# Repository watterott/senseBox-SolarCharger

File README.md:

# senseBox SolarCharger
SolarCharger extension for the senseBox MCU

* senseBox SolarCharger for up to 2x 18650 LiPo batteries
* 7-24V Solar input voltage
* Open-Source and released under the [Creative Commons Attribution Share-Alike License](https://creativecommons.org/licenses/by-sa/4.0/).
* **[Documentation on learn.watterott.com](https://learn.watterott.com)**

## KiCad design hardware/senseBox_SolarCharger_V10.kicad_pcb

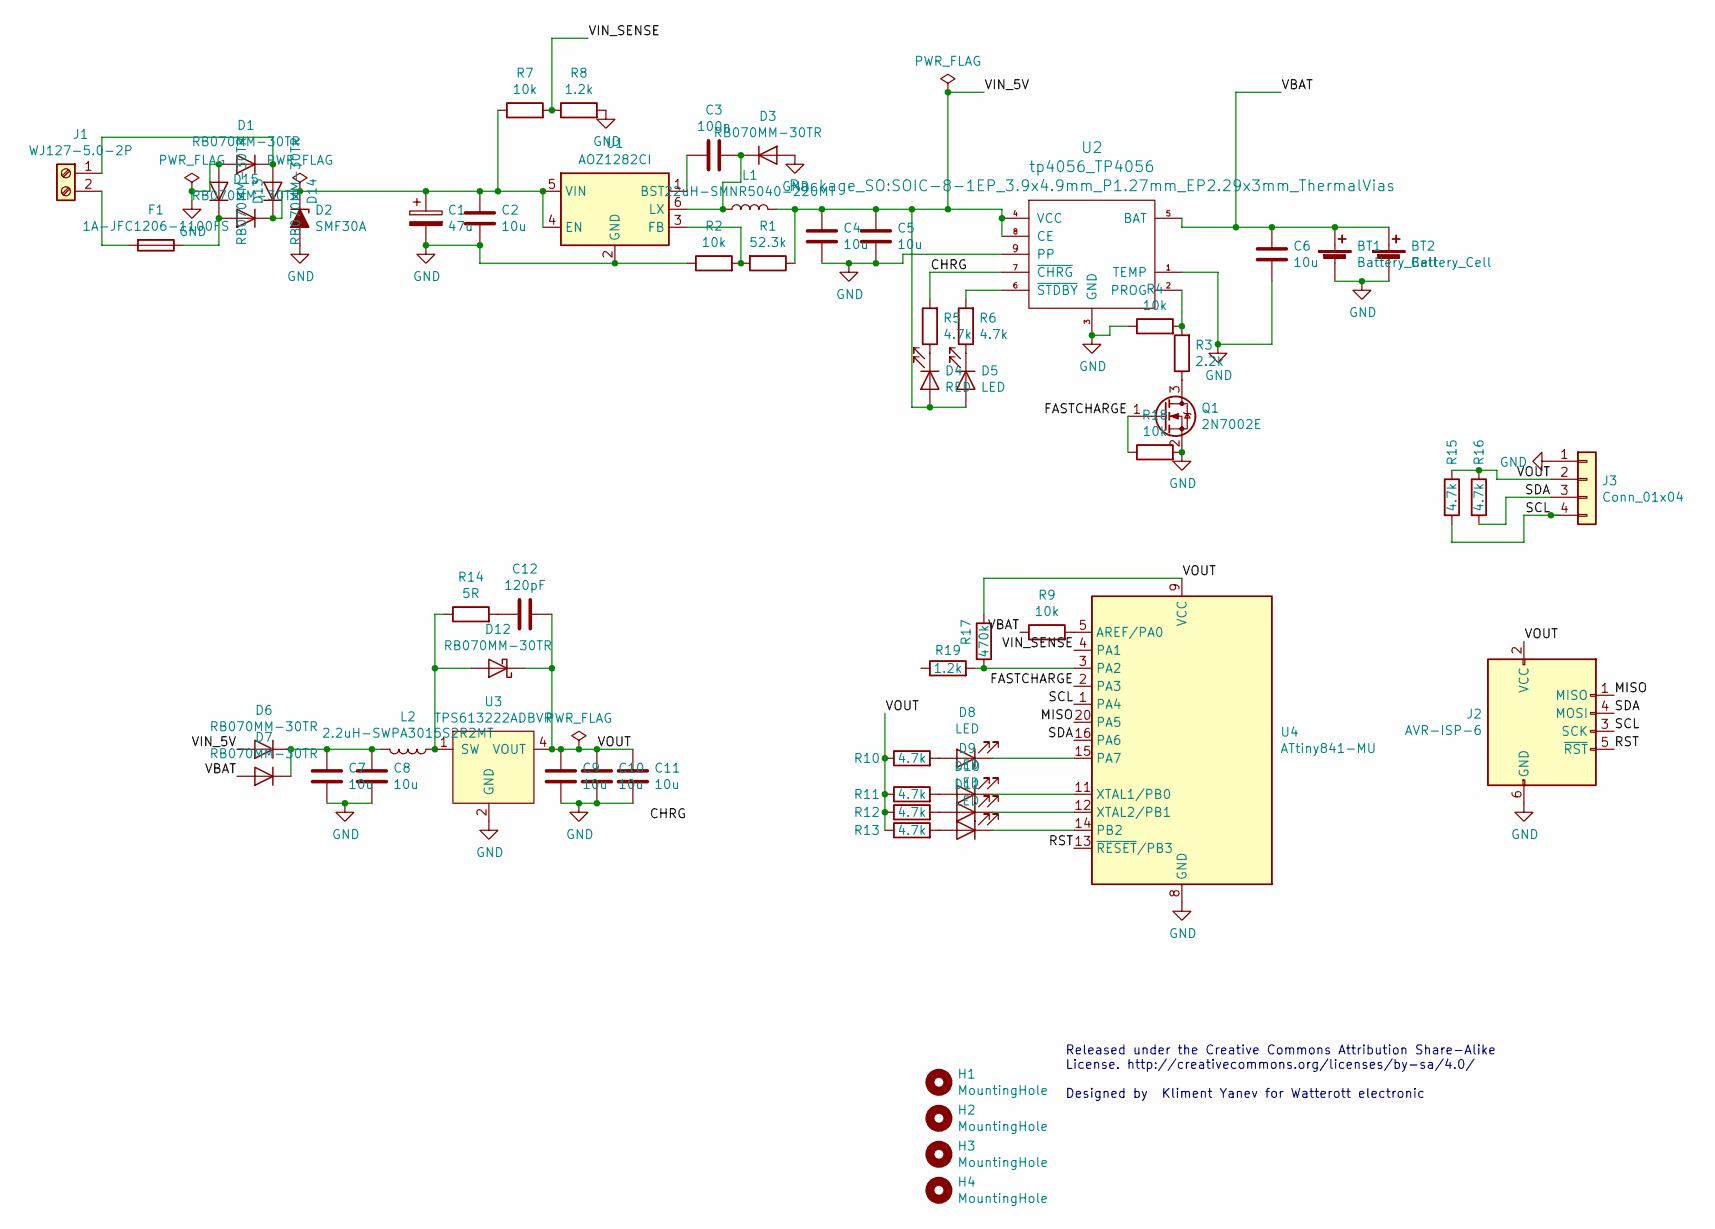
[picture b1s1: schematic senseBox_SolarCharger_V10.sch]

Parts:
BT1, BT2: Battery_Cell; Keystone-54x2-18650
C1: 47u; C_6.3MM
C2, C4, C5, C6, C7, C8, C9, C10, C11: 10u; C1206
C3: 100n; C0603
C12: 120pF; C0603
D1, D6, D7, D13, D14, D15: RB070MM-30TR; D_SOD-123
D2: SMF30A; SOD123
D3, D12: RB070MM-30TR; SOD123
D4: RED; LED_0603_1608Metric
D5, D8, D9, D10, D11: LED; LED_0603_1608Metric
F1: 1A-JFC1206-1100FS; Fuse_1206_3216Metric_Castellated
H1, H2, H3, H4: MountingHole; MountingHole_3.5mm
J1: WJ127-5.0-2P; TerminalBlock_Altech_AK300-2_P5.00mm
J2: AVR-ISP-6; MA03-2
J3: Conn_01x04; JST_B4B-PH-SM4-TB
L1: 22uH-SMNR5040-220MT; L_Wuerth_WE-PD2-Typ-MS
L2: 2.2uH-SWPA3015S2R2MT; L_Neosid_SMS-ME3010
Q1: 2N7002E; SOT-23
R1: 52.3k; R_0603_1608Metric
R2, R4, R7, R9, R18: 10k; R_0603_1608Metric
R3: 2.2k; R_0603_1608Metric
R5, R6, R10, R11, R12, R13, R15, R16: 4.7k; R_0603_1608Metric
R8, R19: 1.2k; R_0603_1608Metric
R14: 5R; R_0603_1608Metric
R17: 470k; R_0603_1608Metric
U1: AOZ1282CI; SOT23-6
U2: tp4056_TP4056; SOIC-8-1EP_3.9x4.9mm_P1.27mm_EP2.29x3mm_ThermalVias
U3: TPS613222ADBVR; SOT23-5
U4: ATtiny841-MU; QFN20-PAD

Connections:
/CHRG: R5.2, R19.1, U2.7 (~CHRG)
/FASTCHARGE: Q1.1 (G), R18.1, U4.2 (PA3)
/MISO: J2.1 (MISO), U4.20 (PA5)
/RST: J2.5 (~RST), U4.13 (~RESET~/PB3)
/SCL: J2.3 (SCK), J3.4, R15.2, U4.1 (PA4)
/SDA: J2.4 (MOSI), J3.3, R16.2, U4.16 (PA6)
/VBAT: BT1.1 (+), BT2.1 (+), C6.1, D7.2 (A), R9.1, U2.5 (BAT)
/VIN_5V: C4.1, C5.1, D4.2 (A), D5.2 (A), D6.2 (A), L1.2, R1.1, U2.4 (VCC), U2.8 (CE)
/VIN_SENSE: R7.2, R8.1, U4.4 (PA1)
/VOUT: C9.1, C10.1, C11.1, C12.1, D12.1 (K), J2.2 (VCC), J3.2, R10.1, R11.1, R12.1, R13.1, R15.1, R16.1, R17.1, U3.4 (VOUT), U4.9 (VCC)
GND: BT1.2 (-), BT2.2 (-), C1.2, C2.2, C4.2, C5.2, C6.2, C7.2, C8.2, C9.2, C10.2, C11.2, D1.2 (A), D2.2 (A), D3.2 (A), D13.2 (A), J2.6 (GND), J3.1, Q1.2 (S), R2.1, R4.1, R8.2, R18.2, U1.2 (GND), U2.1 (TEMP), U2.3 (GND), U2.9 (PP), U3.2 (GND), U4.8 (GND), U4.21 (GND)
unnamed: C1.1, C2.1, D2.1 (K), D14.1 (K), D15.1 (K), R7.1, U1.4 (EN), U1.5 (VIN)
unnamed: C3.1, D3.1 (K), L1.1, U1.6 (LX)
unnamed: C3.2, U1.1 (BST)
unnamed: C7.1, C8.1, D6.1 (K), D7.1 (K), L2.2
unnamed: C12.2, R14.2
unnamed: D1.1 (K), D14.2 (A), J1.1
unnamed: D4.1 (K), R5.1
unnamed: D5.1 (K), R6.1
unnamed: D8.1 (K), U4.15 (PA7)
unnamed: D8.2 (A), R10.2
unnamed: D9.1 (K), U4.11 (XTAL1/PB0)
unnamed: D9.2 (A), R11.2
unnamed: D10.1 (K), U4.12 (XTAL2/PB1)
unnamed: D10.2 (A), R12.2
unnamed: D11.1 (K), U4.14 (PB2)
unnamed: D11.2 (A), R13.2
unnamed: D12.2 (A), L2.1, R14.1, U3.1 (SW)
unnamed: D13.1 (K), D15.2 (A), F1.1
unnamed: F1.2, J1.2
unnamed: Q1.3 (D), R3.1
unnamed: R1.2, R2.2, U1.3 (FB)
unnamed: R3.2, R4.2, U2.2 (PROG)
unnamed: R6.2, U2.6 (~STDBY)
unnamed: R9.2, U4.5 (AREF/PA0)
unnamed: R17.2, R19.2, U4.3 (PA2)

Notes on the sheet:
Released under the Creative Commons Attribution Share-Alike License. http://creativecommons.org/licenses/by-sa/4.0/ Designed by Kliment Yanev for Watterott electronic

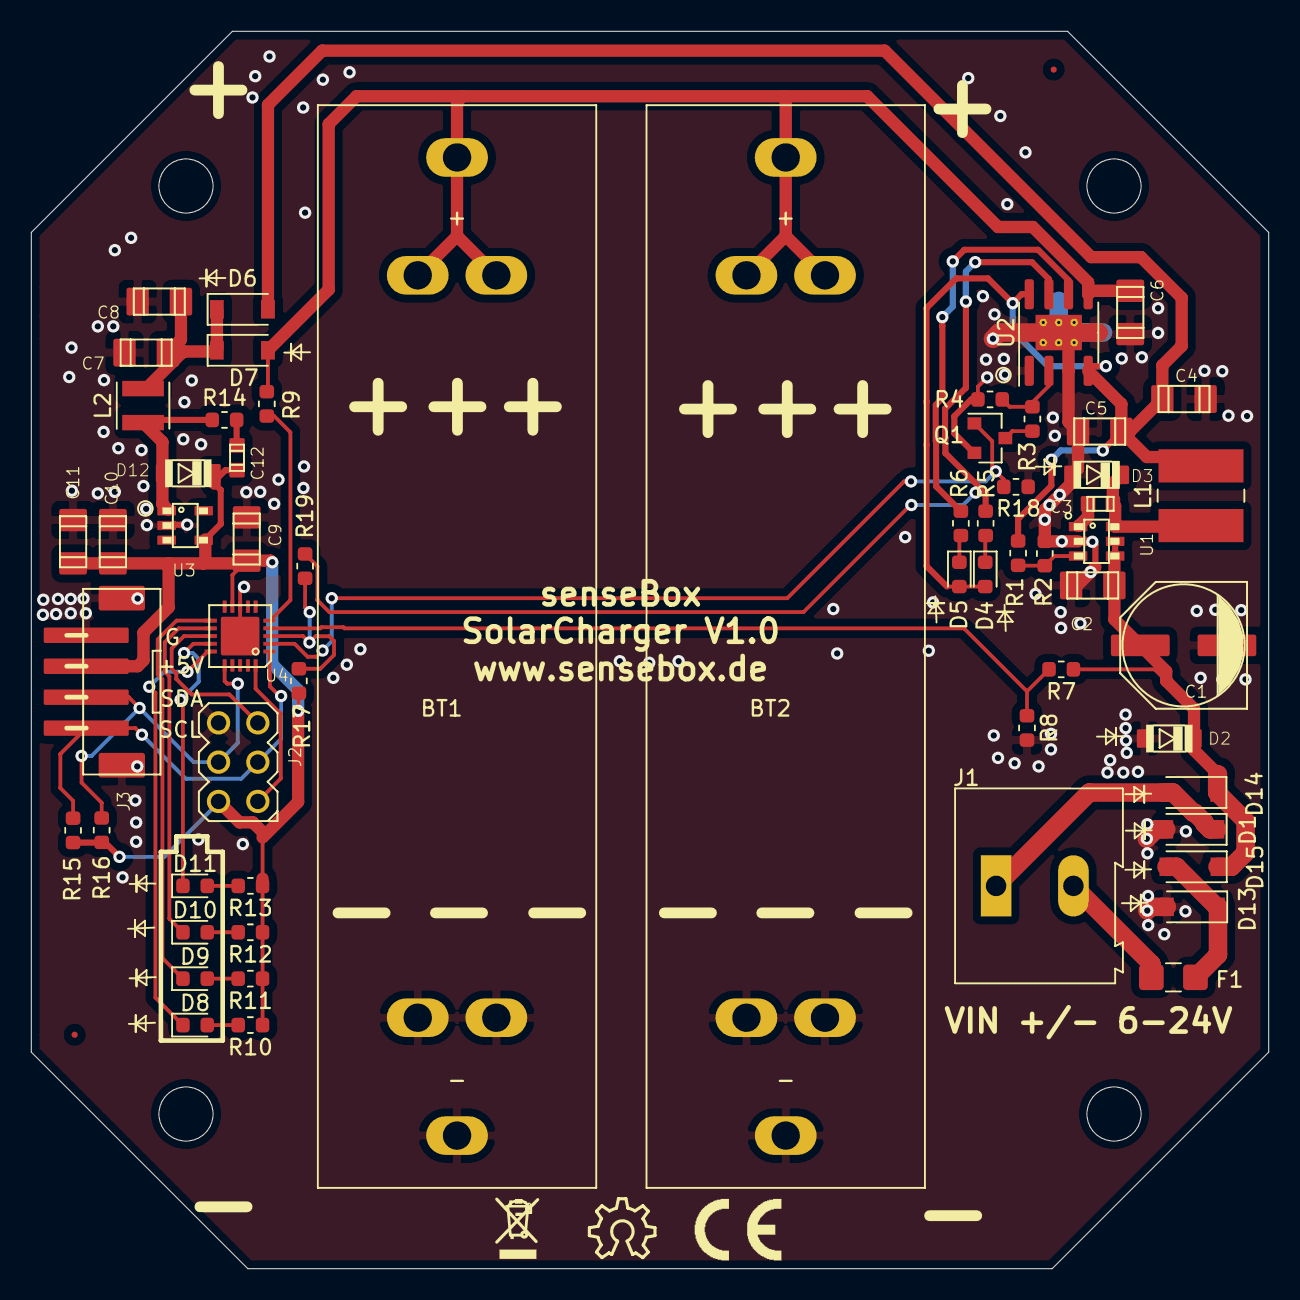
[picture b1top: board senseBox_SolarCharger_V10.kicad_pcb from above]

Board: 2 copper layers, 80.0 x 80.0 mm, 63 parts (0 on the bottom side), 36 nets.

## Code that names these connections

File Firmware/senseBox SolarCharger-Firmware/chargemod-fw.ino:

/*
 * Using ATtinycore, Attiny 841, No bootloader, 8MHz
 * 
 * 
 * Charge controller for sensebox power module. Functionalities:
 * Set PA3 to output low
 * Set PA2 to input, pullup
 * Set PA0, PA1, to analog input
 * Check temp, if temp above 12*C enable fast charge (PA3 high), 
 * if temp below 8*C disable fast charge (PA3 low)
 * Measure incoming voltage on PA1
 * Set PA7, PB0, PB1, PB2 to output high
 * Measure cell voltage on PA0
 * If cell voltage over 3.2V PA7 low
 * If cell voltage over 3.6V PB0 low
 * If cell voltage over 3.7V PB1 low
 * If cell voltage over 3.9V PB2 low
 * Check status for charge
 * Provide I2C i/f with following info:
 * - Register 0: cell voltage, 20mV/LSB
 * - Register 1: input voltage, 100mV/LSB
 * - Register 2: status bits: [B,I,L3,L2,L1,L0,F,C]
 *    B=battery present >2.8V<4.8V
 *    I=Input voltage present >4.5V
 *    L0-L3=battery status LEDs
 *    F=Fast charge enabled
 *    C=Charging
 * - Register 3: temperature in C, signed 8-bit

*/

#include <Wire.h>
#define SLAVE_ADDRESS 0x32
#define TEMP_OFFSET   275

volatile uint8_t i2creg[]={0x00,0x00,0x00,0x00};
volatile char i2cindex=0;

void setup() {
  // put your setup code here, to run once:
  pinMode(PA0, INPUT);
  pinMode(PA1, INPUT);
  pinMode(PA2, INPUT);
  pinMode(0, OUTPUT);
  pinMode(1, OUTPUT);
  pinMode(2, OUTPUT);
  pinMode(3, OUTPUT);
  pinMode(7, OUTPUT);
  digitalWrite(0,HIGH);
  digitalWrite(1,HIGH);
  digitalWrite(2,HIGH);
  digitalWrite(3,HIGH);
  digitalWrite(7,LOW);
  digitalWrite(PA2,HIGH);//pullup
  digitalWrite(PA0,LOW);//no pullup
  digitalWrite(PA1,LOW);//no pullup
  Wire.begin(SLAVE_ADDRESS);
  Wire.onRequest(requestEvent);
  Wire.onReceive(receiveEvent);
  
}

void loop() {
  uint8_t flags=0;
  // put your main code here, to run repeatedly:
  analogReference(INTERNAL1V1);
  analogRead(0x0C);
  delay(10);
  analogRead(0x0C);
  uint32_t temp_raw=analogRead(0x0C);
  int temp=(int)temp_raw-TEMP_OFFSET;
  i2creg[3]=temp;
  // 1LSB/C, calibrate if necessary

  analogReference(DEFAULT);
  analogRead(0x01);
  delay(10);
  int vin_raw=analogRead(0x01);
  //1024 LSBs, 5V VREF, 4.88mV/LSB
  //VIN is a 10k/1.2k voltage divider
  //VIN scaling factor is 9.3
  //vin_raw therefore has 4.88*9.3=45.54mV/LSB
  //we want vin in 100mV increments so we need to multiply by 0.45
  int vin=0.45*vin_raw;
  i2creg[1]=vin;
  if(vin>45){
    flags|=(1<<6);
  }else{
    flags&=~(1<<6);
  }
  
  //quick charge when warm enough and voltage >8V
  if(temp>=12 && temp<46 && vin>80){
    digitalWrite(7,HIGH);
    flags|=(1<<1);
  }
  if(temp<=8 || temp>50 || vin<80){
    digitalWrite(7,LOW);//hysteresis
    flags&=~(1<<1);
  }
  
  
  analogRead(0x00);
  uint32_t vbat_raw=analogRead(0x00);
  //1024 LSBs, 5V VREF, 4.88mV/LSB
  //we want vin in 20mV increments so we need to multiply by 0.244
  int vbat=0.244*vbat_raw;
  i2creg[0]=vbat;
  if(vbat>140 && vbat<240){
    flags|=(1<<7);
  }else{
    flags&=~(1<<7);
  }
  
  if(digitalRead(PA2)==LOW && vin>45 && vbat>140 && vbat <240){ //is battery charging - only possible if supply voltage high enough and battery present
    flags|=(1);
  }else{
    flags&=~(1);
  }
  
  
  if(vbat>160){
    digitalWrite(3,LOW);
    flags|=(1<<(2)); 
  }else{
    digitalWrite(3,HIGH);
    flags&=~(1<<(2)); 
  }
  if(vbat>180){
    digitalWrite(0,LOW);
    flags|=(1<<(3)); 
  }else{
    digitalWrite(0,HIGH);
    flags&=~(1<<(3)); 
  }
  if(vbat>185){
    digitalWrite(1,LOW);
    flags|=(1<<(4)); 
  }else{
    digitalWrite(1,HIGH);
    flags&=~(1<<(4)); 
  }
  if(vbat>195){
    digitalWrite(2,LOW);
    flags|=(1<<(5)); 
  }else{
    digitalWrite(2,HIGH);
    flags&=~(1<<(5)); 
  }
  i2creg[2]=flags;
  delay(100);
  
}

void receiveEvent()
{
  if(Wire.available()){
    i2cindex=Wire.read();
  }
}

void requestEvent()

{
     if(i2cindex>3)i2cindex=0;
     Wire.write(i2creg+i2cindex, 4-i2cindex);
     i2cindex=0;

}

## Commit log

2020-10-05 Add files via upload
    first commit
2020-10-05 Add files via upload
    added PCB image
2020-10-07 added PDF doc
2022-07-01 moved gerber files
2022-07-01 updated file format
